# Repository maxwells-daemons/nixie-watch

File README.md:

# Nixie Watch

The KiCad design files for a nixie-tube wristwatch. The mechanical design can be found at [this Onshape link](https://cad.onshape.com/documents/168decd161ae34bc06a36311/w/d9452b42c2f2de4575e19b2f/e/99e0d669777a0ebc0bf45485).

## Organization

 - `kicad/board`: The primary PCB design.
 - `kicad/riser`: The design for a riser board to mount nixie tubes and route their connections.

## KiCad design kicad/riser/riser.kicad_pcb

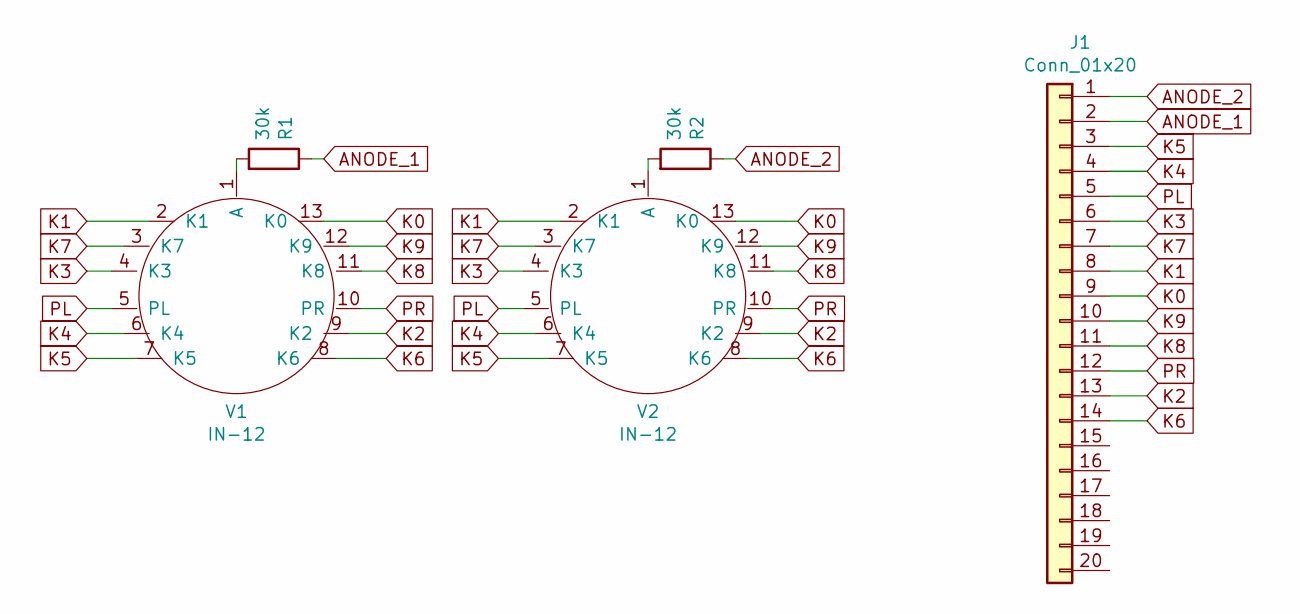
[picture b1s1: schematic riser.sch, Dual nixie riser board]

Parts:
J1: Conn_01x20; BC075-20
R1, R2: 30k; R_0805_2012Metric_Pad1.20x1.40mm_HandSolder
V1, V2: IN-12

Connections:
ANODE_1: J1.2, R1.1
ANODE_2: J1.1, R2.1
K0: J1.9, V1.13 (K0), V2.13 (K0)
K1: J1.8, V1.2 (K1), V2.2 (K1)
K2: J1.13, V1.9 (K2), V2.9 (K2)
K3: J1.6, V1.4 (K3), V2.4 (K3)
K4: J1.4, V1.6 (K4), V2.6 (K4)
K5: J1.3, V1.7 (K5), V2.7 (K5)
K6: J1.14, V1.8 (K6), V2.8 (K6)
K7: J1.7, V1.3 (K7), V2.3 (K7)
K8: J1.11, V1.11 (K8), V2.11 (K8)
K9: J1.10, V1.12 (K9), V2.12 (K9)
unnamed: R1.2, V1.1 (A)
unnamed: R2.2, V2.1 (A)
PL: J1.5, V1.5 (PL), V2.5 (PL)
PR: J1.12, V1.10 (PR), V2.10 (PR)

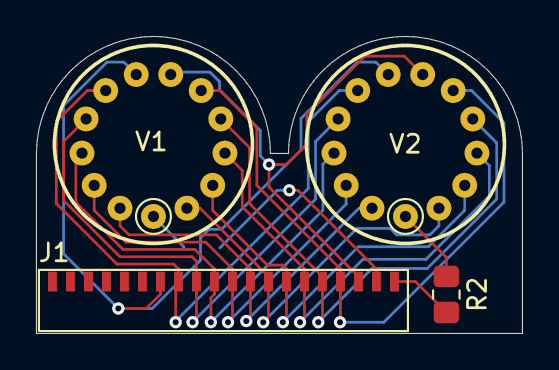
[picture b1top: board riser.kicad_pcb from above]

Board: 2 copper layers, 27.0 x 16.5 mm, 5 parts (1 on the bottom side), 16 nets.

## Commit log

2021-01-22 Add organization info to README
2021-01-22 Add Onshape link to README
